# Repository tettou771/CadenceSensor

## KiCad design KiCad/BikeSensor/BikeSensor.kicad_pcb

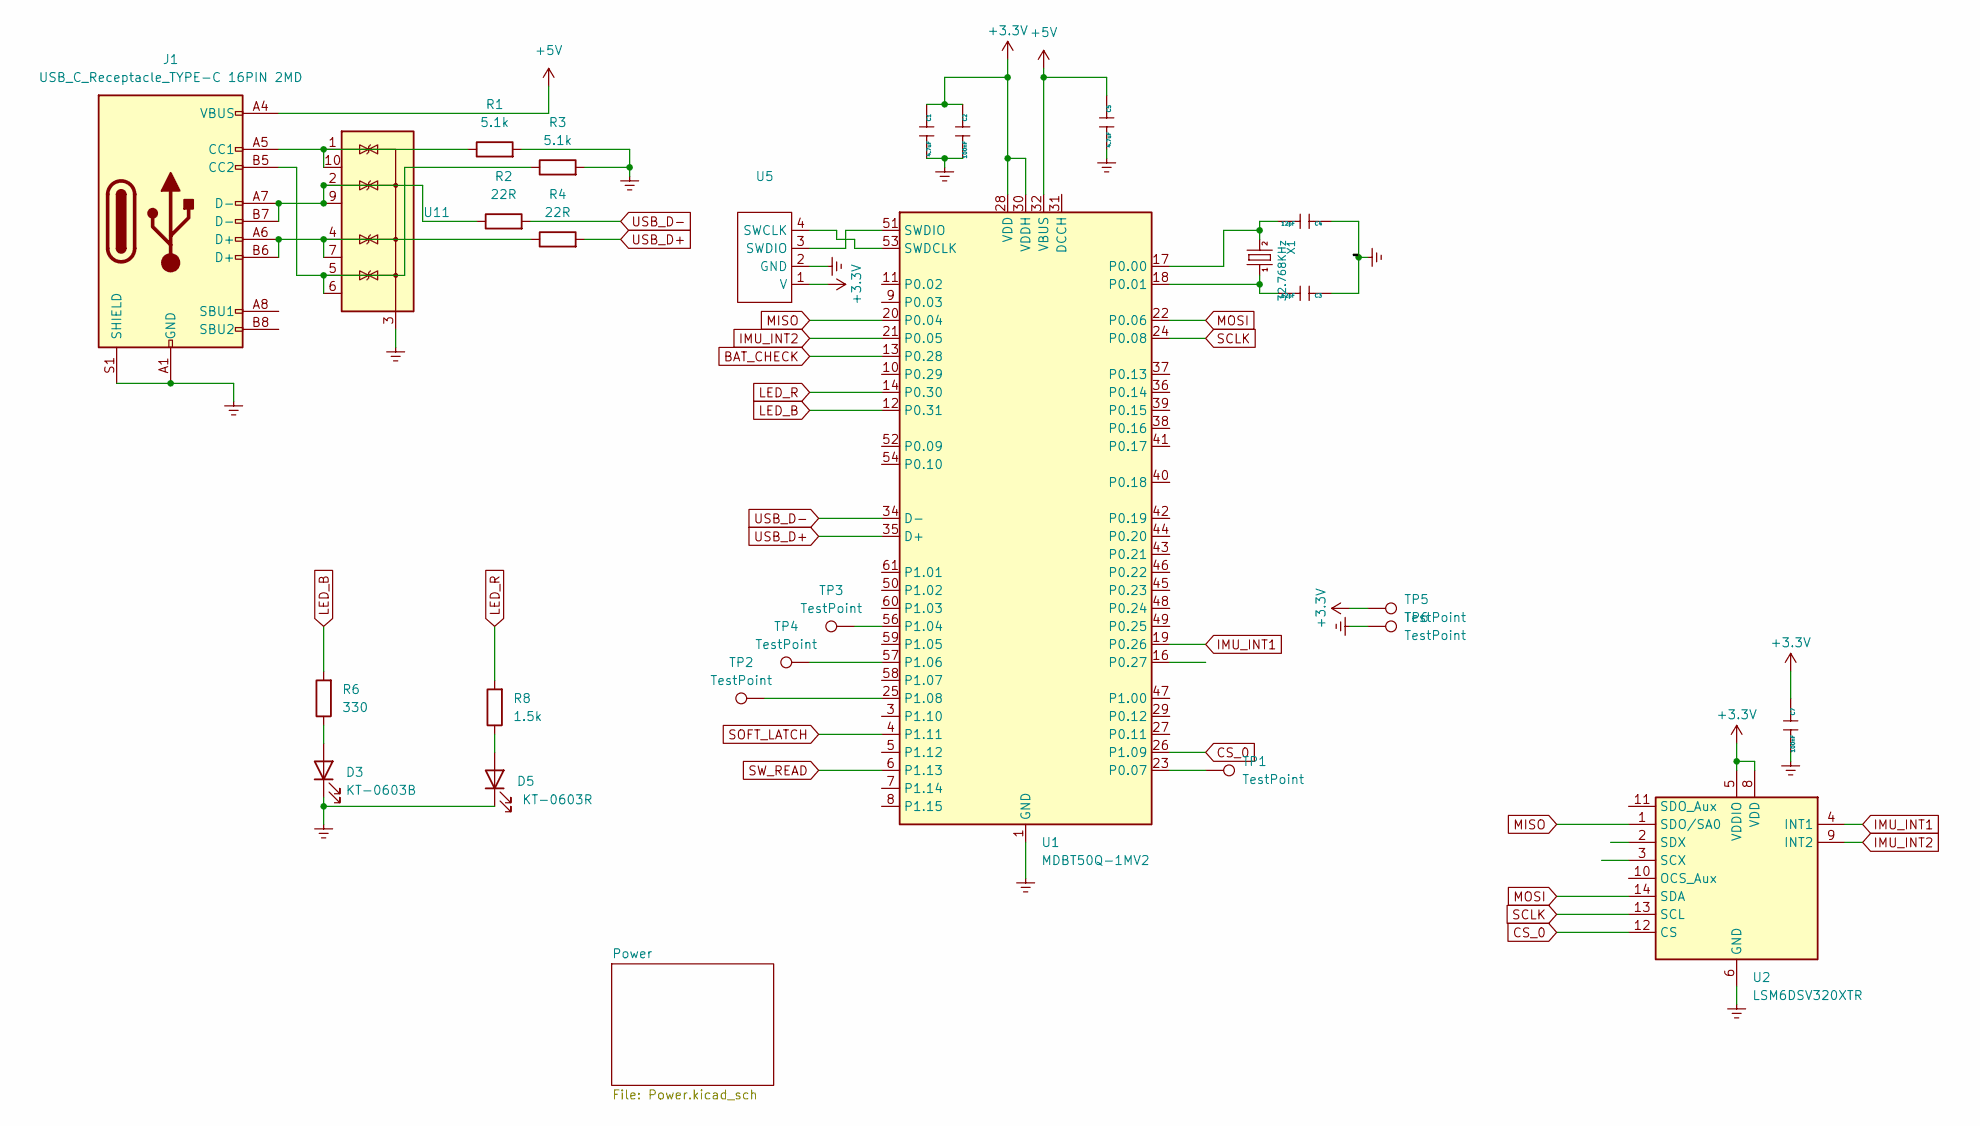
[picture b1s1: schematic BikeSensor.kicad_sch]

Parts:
C1, C5: 4.7uF; C_0402_1005Metric
C2, C7: 100nF; C_0402_1005Metric
C3, C4: 12pF; C_0402_1005Metric
D3: KT-0603B; LED_0603_1608Metric
D5: KT-0603R; LED_0603_1608Metric
J1: USB_C_Receptacle_TYPE-C 16PIN 2MD
R1, R3: 5.1k; R_0402_1005Metric
R2, R4: 22R; R_0402_1005Metric
R6: 330; R_0402_1005Metric
R8: 1.5k; R_0402_1005Metric
TP1, TP2, TP3, TP4, TP5, TP6: TestPoint; TestPoint_Pad_D1.5mm
U1: MDBT50Q-1MV2; Raytac_MDBT50Q
U2: LSM6DSV320XTR; LGA-14_3x2.5mm_P0.5mm_LayoutBorder3x4y
U5: ICSP_SWD_127
U11: TPD4E02B04DQA; USON-10_2.5x1.0mm_P0.5mm
X1: 32.768KHz; Crystal_SMD_3215-2Pin_3.2x1.5mm

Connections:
+3.3V: C1.1, C2.1, C7.1, TP5.1 (1_1), U1.28 (VDD), U1.30 (VDDH), U2.5 (VDDIO), U2.8 (VDD), U5.1 (V); also elsewhere on the board
+5V: C5.1, J1.A4 (VBUS), J1.A9 (VBUS), J1.B4 (VBUS), J1.B9 (VBUS), U1.32 (VBUS); also elsewhere on the board
BAT_CHECK: U1.13 (P0.28); also elsewhere on the board
CS_0: U1.26 (P1.09), U2.12 (CS)
GND_POWER: C1.2, C2.2, C3.1, C4.1, C5.2, C7.2, D3.1 (K), D5.1 (K), J1.A1 (GND), J1.A12 (GND), J1.B1 (GND), J1.B12 (GND), J1.S1 (SHIELD), R1.2, R3.2, TP6.1 (1_1), U1.1 (GND), U1.2 (GND), U1.15 (GND), U1.33 (GND), U1.55 (GND), U2.6 (GND), U2.7 (GND), U5.2 (GND), U11.3 (G), U11.8 (G); also elsewhere on the board
IMU_INT1: U1.19 (P0.26), U2.4 (INT1)
IMU_INT2: U1.21 (P0.05), U2.9 (INT2)
LED_B: R6.2, U1.12 (P0.31)
LED_R: R8.2, U1.14 (P0.30)
MISO: U1.20 (P0.04), U2.1 (SDO/SA0)
MOSI: U1.22 (P0.06), U2.14 (SDA)
unnamed: D3.2 (A), R6.1
unnamed: D5.2 (A), R8.1
unnamed: J1.A5 (CC1), R1.1, U11.1 (IO1), U11.10 (NC)
unnamed: J1.B5 (CC2), R3.1, U11.5 (IO4), U11.6 (NC)
unnamed: C4.2, U1.17 (P0.00), X1.2
unnamed: C3.2, U1.18 (P0.01), X1.1
unnamed: TP1.1 (1_1), U1.23 (P0.07)
unnamed: TP3.1 (1_1), U1.56 (P1.04)
unnamed: TP4.1 (1_1), U1.57 (P1.06)
unnamed: TP2.1 (1_1), U1.25 (P1.08)
unnamed: U1.53 (SWDCLK), U5.4 (SWCLK)
unnamed: U1.51 (SWDIO), U5.3 (SWDIO)
unnamed: J1.A7 (D-), J1.B7 (D-), R2.1, U11.2 (IO2), U11.9 (NC)
unnamed: J1.A6 (D+), J1.B6 (D+), R4.1, U11.4 (IO3), U11.7 (NC)
SCLK: U1.24 (P0.08), U2.13 (SCL)
SOFT_LATCH: U1.4 (P1.11); also elsewhere on the board
SW_READ: U1.6 (P1.13); also elsewhere on the board
USB_D+: R4.2, U1.35 (D+)
USB_D-: R2.2, U1.34 (D-)

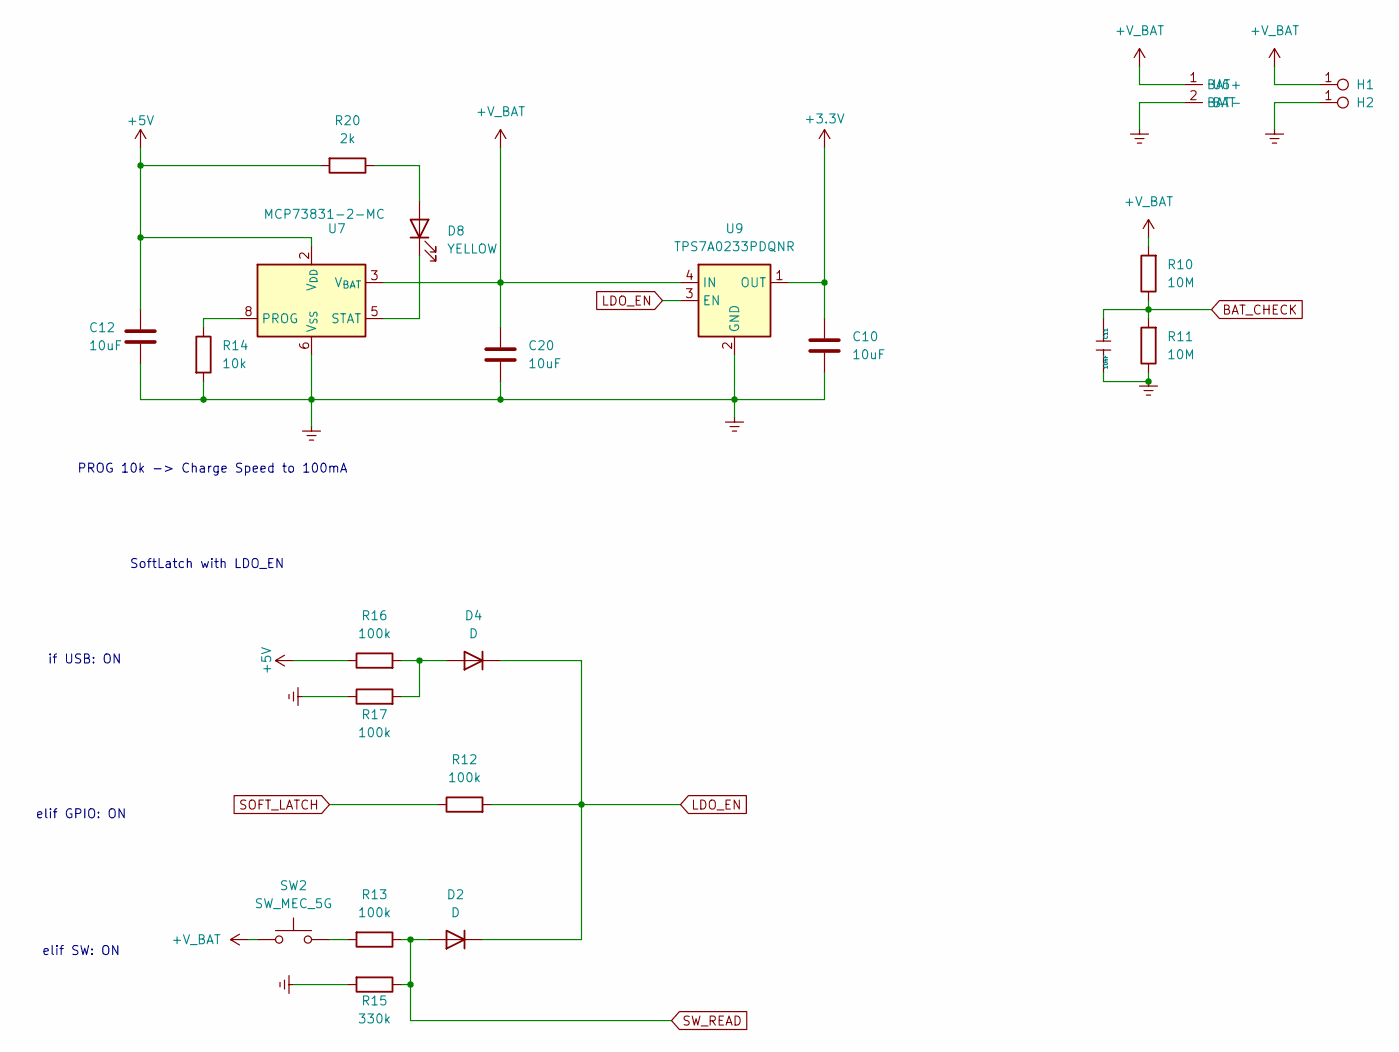
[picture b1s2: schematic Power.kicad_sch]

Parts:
C10, C12, C20: 10uF; C_0603_1608Metric
C11: 10nF; C_0402_1005Metric
D2, D4: D; D_SOD-323
D8: YELLOW; LED_0603_1608Metric
H1, H2: TH_0.7mm
R10, R11: 10M; R_0402_1005Metric
R12, R13, R16, R17: 100k; R_0402_1005Metric
R14: 10k; R_0402_1005Metric
R15: 330k; R_0402_1005Metric
R20: 2k; R_0402_1005Metric
SW2: SW_MEC_5G; SW_SPST_B3U-1000P
U6: BAT; SPK_PAD
U7: MCP73831-2-MC; DFN-8-1EP_3x2mm_P0.5mm_EP1.7x1.4mm
U9: TPS7A0233PDQNR; Texas_X2SON-4_1x1mm_P0.65mm

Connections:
+3.3V: C10.1, U9.1 (OUT); also elsewhere on the board
+5V: C12.1, R16.1, R20.2, U7.1 (V_{DD}), U7.2 (V_{DD}); also elsewhere on the board
+V_BAT: C20.1, H1.1, R10.2, SW2.1 (A), U6.1 (BAT+), U7.3 (V_{BAT}), U7.4 (V_{BAT}), U9.4 (IN)
BAT_CHECK: C11.1, R10.1, R11.2; also elsewhere on the board
GND_POWER: C10.2, C11.2, C12.2, C20.2, H2.1, R11.1, R14.2, R15.2, R17.1, U6.2 (BAT-), U7.6 (V_{SS}), U9.2 (GND), U9.5 (GND); also elsewhere on the board
LDO_EN: D2.1 (K), D4.1 (K), R12.2, U9.3 (EN)
unnamed: D4.2 (A), R16.2, R17.2
unnamed: D8.2 (A), R20.1
unnamed: D8.1 (K), U7.5 (STAT)
unnamed: R13.2, SW2.2 (B), SW2.3 (B)
unnamed: R14.1, U7.8 (PROG)
SOFT_LATCH: R12.1; also elsewhere on the board
SW_READ: D2.2 (A), R13.1, R15.1; also elsewhere on the board

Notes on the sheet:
elif SW: ON
PROG 10k -> Charge Speed to 100mA
elif GPIO: ON
if USB: ON
SoftLatch with LDO_EN

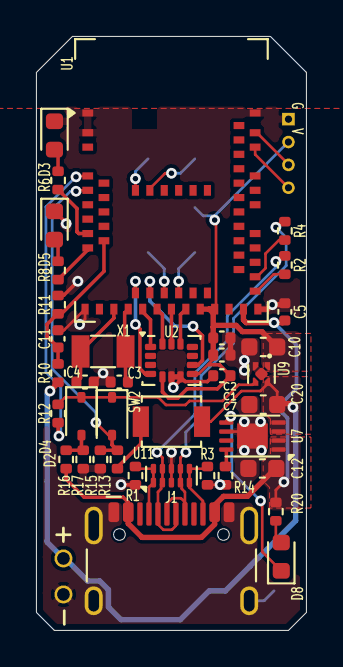
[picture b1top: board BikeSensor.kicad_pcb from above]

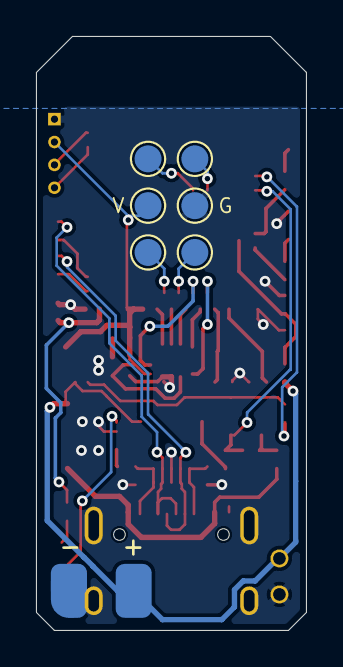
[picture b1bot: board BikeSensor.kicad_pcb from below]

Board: 2 copper layers, 15.0 x 33.0 mm, 48 parts (7 on the bottom side), 37 nets.

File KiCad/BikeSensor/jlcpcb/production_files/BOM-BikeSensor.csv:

Comment,Designator,Footprint,LCSC,Quantity
1.5k,R8,R_0402_1005Metric,C25867,1
100k,"R12,R13,R16,R17",R_0402_1005Metric,C25741,4
100nF,"C2,C7",C_0402_1005Metric,C1525,2
10M,"R10,R11",R_0402_1005Metric,C26082,2
10k,R14,R_0402_1005Metric,C25744,1
10nF,C11,C_0402_1005Metric,C15195,1
10uF,"C10,C12,C20",C_0603_1608Metric,C19702,3
12pF,"C3,C4",C_0402_1005Metric,C1547,2
22R,"R2,R4",R_0402_1005Metric,C25092,2
2k,R20,R_0402_1005Metric,C4109,1
32.768KHz,X1,Crystal_SMD_3215-2Pin_3.2x1.5mm,C32346,1
330,R6,R_0402_1005Metric,C25104,1
330k,R15,R_0402_1005Metric,C25778,1
4.7uF,"C1,C5",C_0402_1005Metric,C23733,2
5.1k,"R1,R3",R_0402_1005Metric,C25905,2
D,"D2,D4",D_SOD-323,C2128,2
KT-0603B,D3,LED_0603_1608Metric,C2288,1
KT-0603R,D5,LED_0603_1608Metric,C2286,1
LSM6DSV320XTR,U2,LGA-14_3x2.5mm_P0.5mm_LayoutBorder3x4y,C26633007,1
MCP73831-2-MC,U7,DFN-8-1EP_3x2mm_P0.5mm_EP1.7x1.4mm,C150772,1
MDBT50Q-1MV2,U1,Raytac_MDBT50Q,C5118826,1
SW_MEC_5G,SW2,SW_SPST_B3U-1000P,C231329,1
TPD4E02B04DQA,U11,USON-10_2.5x1.0mm_P0.5mm,C106794,1
TPS7A0233PDQNR,U9,Texas_X2SON-4_1x1mm_P0.65mm,C2860046,1
USB_C_Receptacle_TYPE-C 16PIN 2MD,J1,USB_C_Receptacle_TYPE-C 16PIN 2MD,C165948,1
YELLOW,D8,LED_0603_1608Metric,C111340,1

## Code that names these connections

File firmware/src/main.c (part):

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 */
#define SYSTEM_OFF_MS (10 * 60 * 1000)

static const struct gpio_dt_spec led_r = GPIO_DT_SPEC_GET(DT_ALIAS(led_red), gpios);
static const struct gpio_dt_spec led_b = GPIO_DT_SPEC_GET(DT_ALIAS(led_blue), gpios);

/* Green is optional. The RideFormTracker bring-up board carries an RGB LED;
 * the v1 cadence PCB has two discrete LEDs and no green at all. Where there is
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static const struct gpio_dt_spec led_g = GPIO_DT_SPEC_GET(DT_ALIAS(led_green), gpios);
#define LED_BOOT_OK (&led_g)
#else
#define LED_BOOT_OK (&led_b)
#endif

static const struct gpio_dt_spec imu_int1 =
	GPIO_DT_SPEC_GET(DT_PATH(zephyr_user), imu_int1_gpios);

/* The board's own power switch, present only on PCBs that gate their 3.3 V
 * rail. GET_OR leaves these zeroed on boards that do not, and gpio_is_ready_dt()
 * then reports them absent, so one image still builds and runs on both. */
static const struct gpio_dt_spec soft_latch =
	GPIO_DT_SPEC_GET_OR(DT_PATH(zephyr_user), soft_latch_gpios, {0});
static const struct gpio_dt_spec sw_read =
	GPIO_DT_SPEC_GET_OR(DT_PATH(zephyr_user), sw_read_gpios, {0});

static const struct device *console_dev = DEVICE_DT_GET(DT_CHOSEN(zephyr_console));
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
static void leds_init(void)
{
	gpio_pin_configure_dt(&led_r, GPIO_OUTPUT_INACTIVE);
	gpio_pin_configure_dt(&led_b, GPIO_OUTPUT_INACTIVE);
#if DT_NODE_EXISTS(DT_ALIAS(led_green))
	gpio_pin_configure_dt(&led_g, GPIO_OUTPUT_INACTIVE);
#endif
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
static void power_latch_init(void)
{
	if (!gpio_is_ready_dt(&soft_latch)) {
		return; /* a board whose rail is always on */
	}

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	/* No pull. SW_READ sits on the 100k/330k divider off the button, which
	 * already defines both levels; an internal pulldown (~13 kohm) would
	 * swamp it and the button would never read as pressed. */
	if (gpio_is_ready_dt(&sw_read) &&
	    gpio_pin_configure_dt(&sw_read, GPIO_INPUT) == 0) {
		pressed = gpio_pin_get_dt(&sw_read) == 1;
	}

	/* Three reasons, and the third is the one that makes System OFF work at
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	 * did before RESETREAS was consulted. */
	latched = pressed || vbus_present() || woke_from_system_off();

	gpio_pin_configure_dt(&soft_latch, latched ? GPIO_OUTPUT_ACTIVE
						   : GPIO_OUTPUT_INACTIVE);

	LOG_INF("power latch %s (button %s, VBUS %s, resetreas 0x%08x%s)",
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	 * definition the thing about to stop reporting is the battery. */
	blink(&led_r, 3, 120);

	if (!gpio_is_ready_dt(&soft_latch)) {
		LOG_ERR("no power latch on this board - cannot switch off");
		return;
	}

	gpio_pin_set_dt(&soft_latch, 0);
	latched = false;

	k_msleep(500);
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{
	int err;

	if (!gpio_is_ready_dt(&imu_int1)) {
		return -ENODEV;
	}

	err = gpio_pin_configure_dt(&imu_int1, GPIO_INPUT);
	if (err) {
		return err;
	}

	err = gpio_pin_interrupt_configure_dt(&imu_int1, GPIO_INT_EDGE_TO_ACTIVE);
	if (err) {
		return err;
	}

	gpio_init_callback(&imu_int1_cb, imu_int1_handler, BIT(imu_int1.pin));

	return gpio_add_callback(imu_int1.port, &imu_int1_cb);
}

static bool recently_moved(void)
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 */
static void maybe_system_off(const struct cadence_state *st)
{
	if (!lsm6dsv_present() || !int1_ok || !gpio_is_ready_dt(&imu_int1)) {
		return; /* nothing could wake us again */
	}

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	k_msleep(50); /* let the console drain */

	ble_csc_set_advertising(false);
	(void)gpio_pin_interrupt_configure_dt(&imu_int1, GPIO_INT_LEVEL_ACTIVE);

	sys_poweroff();
}
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	printk("duty      : sampler %u %% / advertising %u %%  (over %u s)\n",
	       duty_secs ? duty_awake * 100 / duty_secs : 0,
	       duty_secs ? duty_adv * 100 / duty_secs : 0, duty_secs);
	if (gpio_is_ready_dt(&soft_latch)) {
		/* On a board that switches its own rail, "why am I still on"
		 * is a real question with a real answer. */
		printk("power     : latch %s, button %s\n",
		       latched ? "held" : "NOT HELD",
		       !gpio_is_ready_dt(&sw_read) ? "?" :
		       gpio_pin_get_dt(&sw_read) == 1 ? "down" : "up");
	}
	/* Which of the three USB states this is, because "no console" has
	 * three different causes and they need different reactions: no cable,
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		if (st.total_revs != seen_revs) {
			seen_revs = st.total_revs;
			if (usb_present) {
				gpio_pin_set_dt(&led_b, 1);
				led_on = true;
			}
		} else if (led_on) {
			gpio_pin_set_dt(&led_b, 0);
			led_on = false;
		}

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

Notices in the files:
firmware/src/main.c:
SPDX-License-Identifier: Apache-2.0
